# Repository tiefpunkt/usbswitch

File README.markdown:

# USB Switch
The USB Switch will be a device that can be plugged between a PC and a device using USB as a power source. The USB Switch can switch the connected device on and off, controlled by a serial console.

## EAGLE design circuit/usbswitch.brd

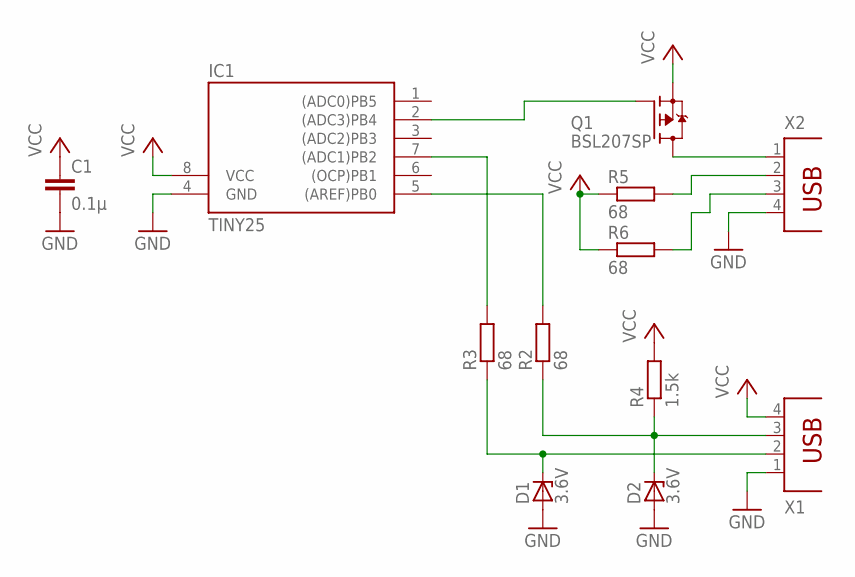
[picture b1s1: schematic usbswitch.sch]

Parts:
C1: 0.1µ; C1206
D1, D2: 3.6V; SOD80C
IC1: TINY25; SOIC8
Q1: BSL207SP; SOT23
R2, R3, R6: 68; R1206
R4: 1.5k; R1206
R5: 68; R1206@1
X1, X2: PN87520

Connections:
GND: C1.2, D1.A, D2.A, IC1.4 (GND), X1.1, X2.4
unnamed: IC1.2 ((ADC3)PB4), Q1.1 (G)
unnamed: Q1.3 (D), X2.1
unnamed: R5.2, X2.2
unnamed: D2.C, R2.1, R4.1, X1.3
unnamed: D1.C, R3.1, X1.2
unnamed: IC1.5 ((AREF)PB0), R2.2
unnamed: IC1.7 ((ADC1)PB2), R3.2
unnamed: R6.2, X2.3
VCC: C1.1, IC1.8 (VCC), Q1.2 (S), R4.2, R5.1, R6.1, X1.4

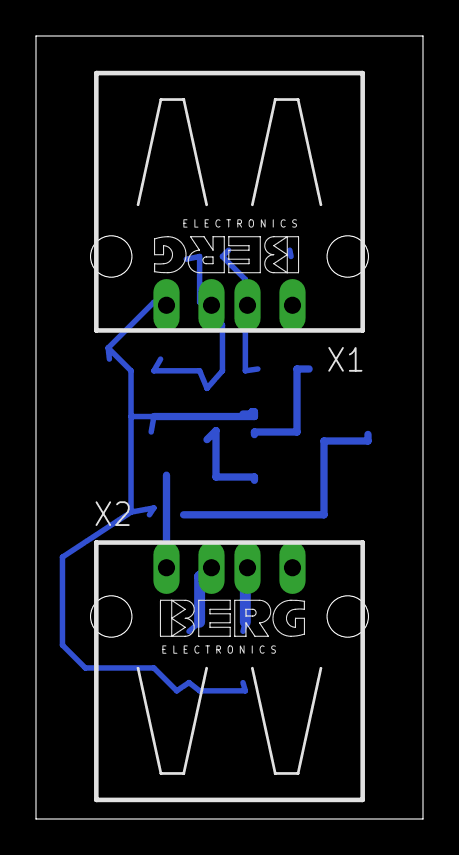
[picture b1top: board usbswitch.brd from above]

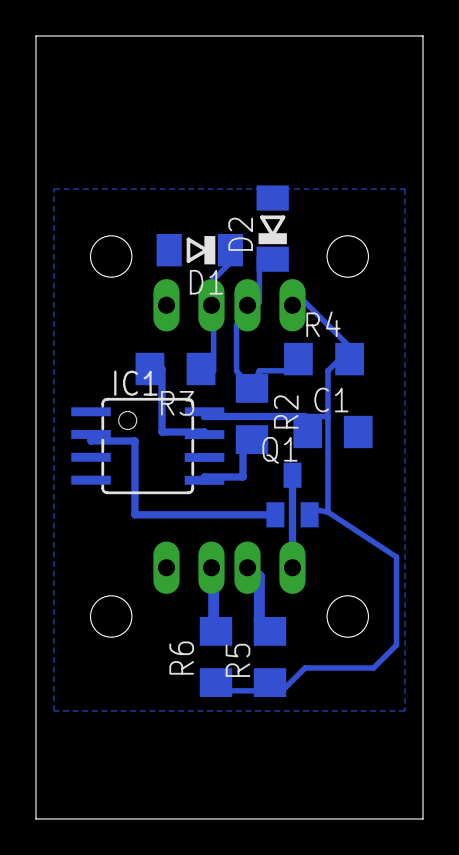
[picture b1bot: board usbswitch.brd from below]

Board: 2 copper layers, 21.5 x 43.5 mm, 12 parts (10 on the bottom side), 10 nets.

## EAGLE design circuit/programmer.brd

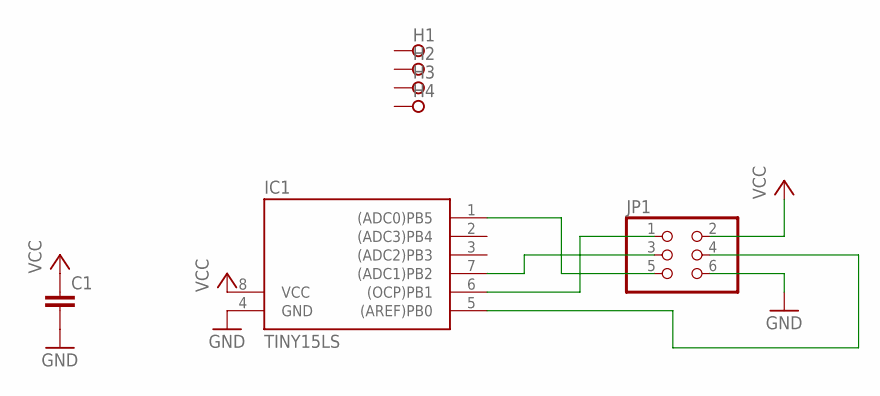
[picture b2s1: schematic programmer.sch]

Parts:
C1: C-EUC1206; C1206
H1, H2, H3, H4: SPECIAL_DRILL_0.1000; PAD_0.1000
IC1: TINY15LS; SOIC8
JP1: PINHD-2X3; 2X03

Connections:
GND: C1.2, IC1.4 (GND), JP1.6
unnamed: IC1.1 ((ADC0)PB5), JP1.5
unnamed: IC1.6 ((OCP)PB1), JP1.1
unnamed: IC1.5 ((AREF)PB0), JP1.4
unnamed: IC1.7 ((ADC1)PB2), JP1.3
VCC: C1.1, IC1.8 (VCC), JP1.2

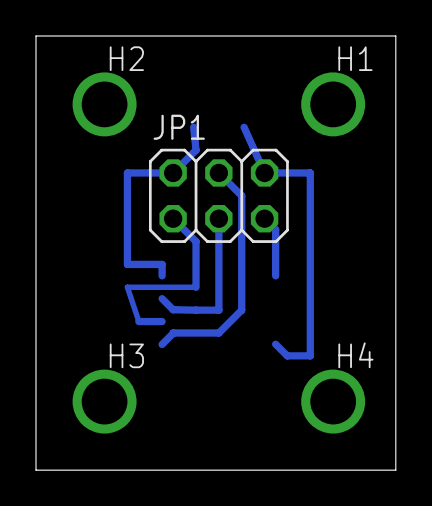
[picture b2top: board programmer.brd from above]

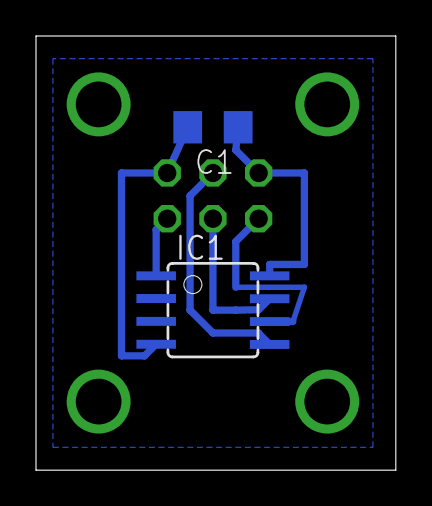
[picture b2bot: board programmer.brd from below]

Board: 2 copper layers, 20.0 x 24.1 mm, 7 parts (2 on the bottom side), 6 nets.

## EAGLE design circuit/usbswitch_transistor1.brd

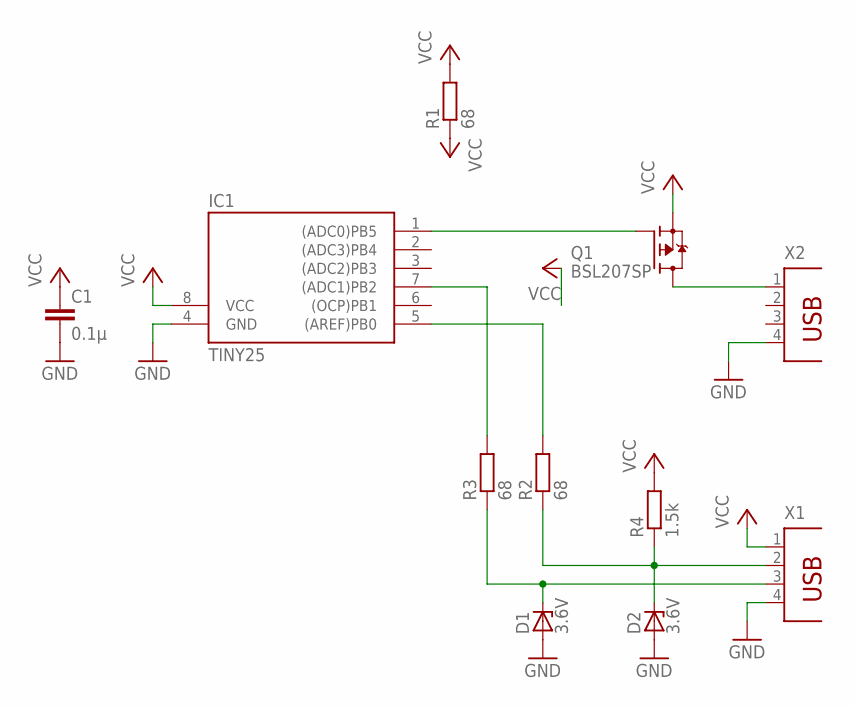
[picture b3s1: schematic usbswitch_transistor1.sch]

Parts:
C1: 0.1µ; C1206
D1, D2: 3.6V; SOD80C
IC1: TINY25; SOIC8
Q1: BSL207SP; SOT23
R1: 68; R1206
R2, R3: 68; R0805
R4: 1.5k; R0805
X1, X2: PN87520

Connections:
GND: C1.2, D1.A, D2.A, IC1.4 (GND), X1.4, X2.4
unnamed: IC1.1 ((ADC0)PB5), Q1.1 (G)
unnamed: Q1.3 (D), X2.1
unnamed: D2.C, R2.1, R4.1, X1.2
unnamed: D1.C, R3.1, X1.3
unnamed: IC1.5 ((AREF)PB0), R2.2
unnamed: IC1.7 ((ADC1)PB2), R3.2
VCC: C1.1, IC1.8 (VCC), Q1.2 (S), R1.1, R1.2, R4.2, X1.1

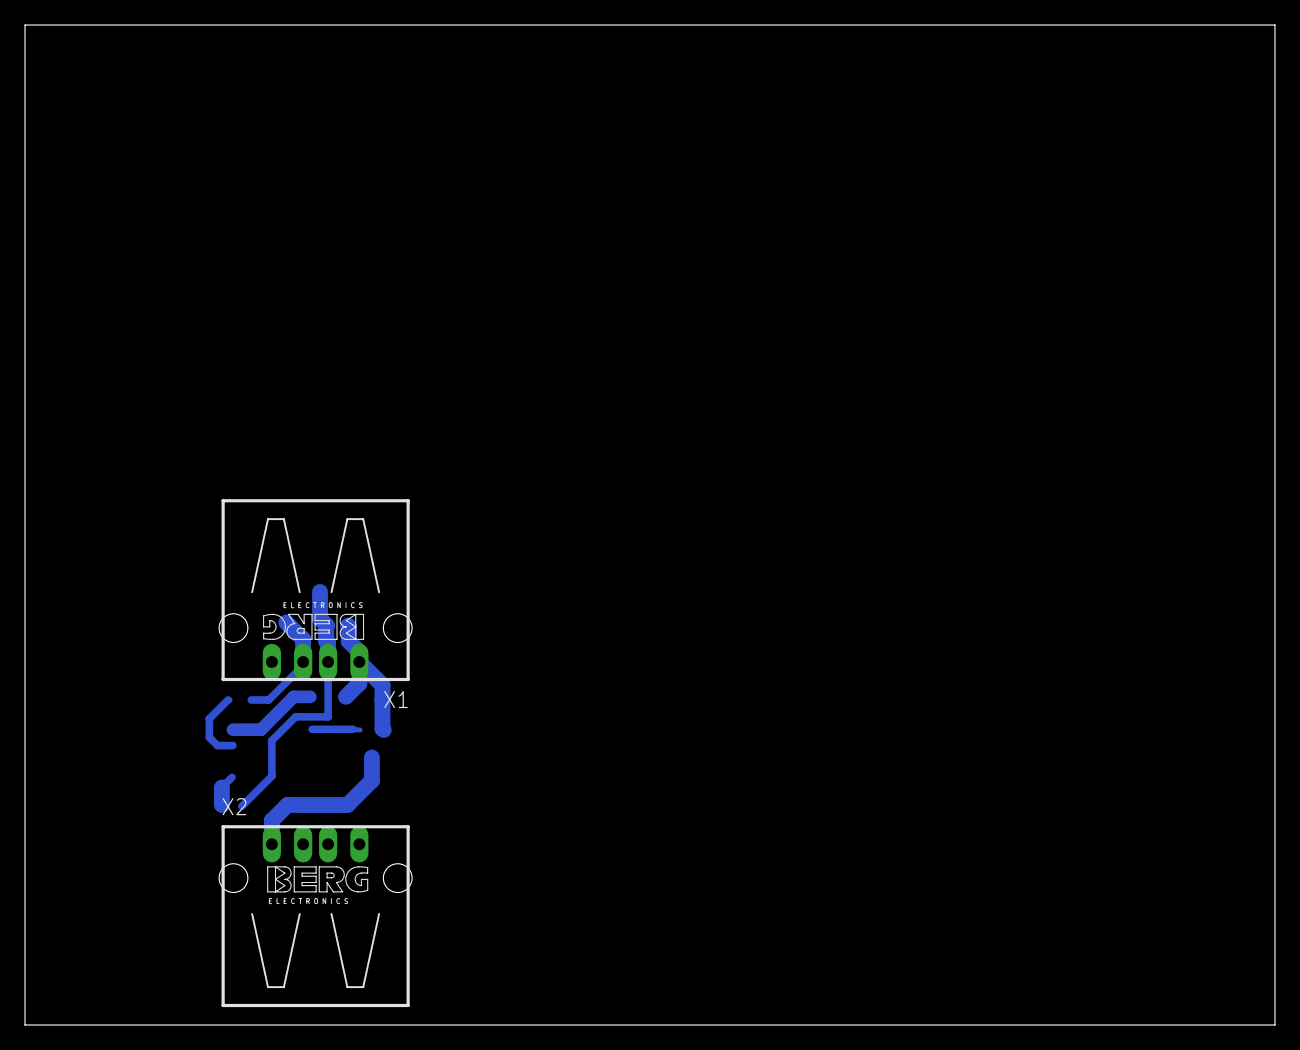
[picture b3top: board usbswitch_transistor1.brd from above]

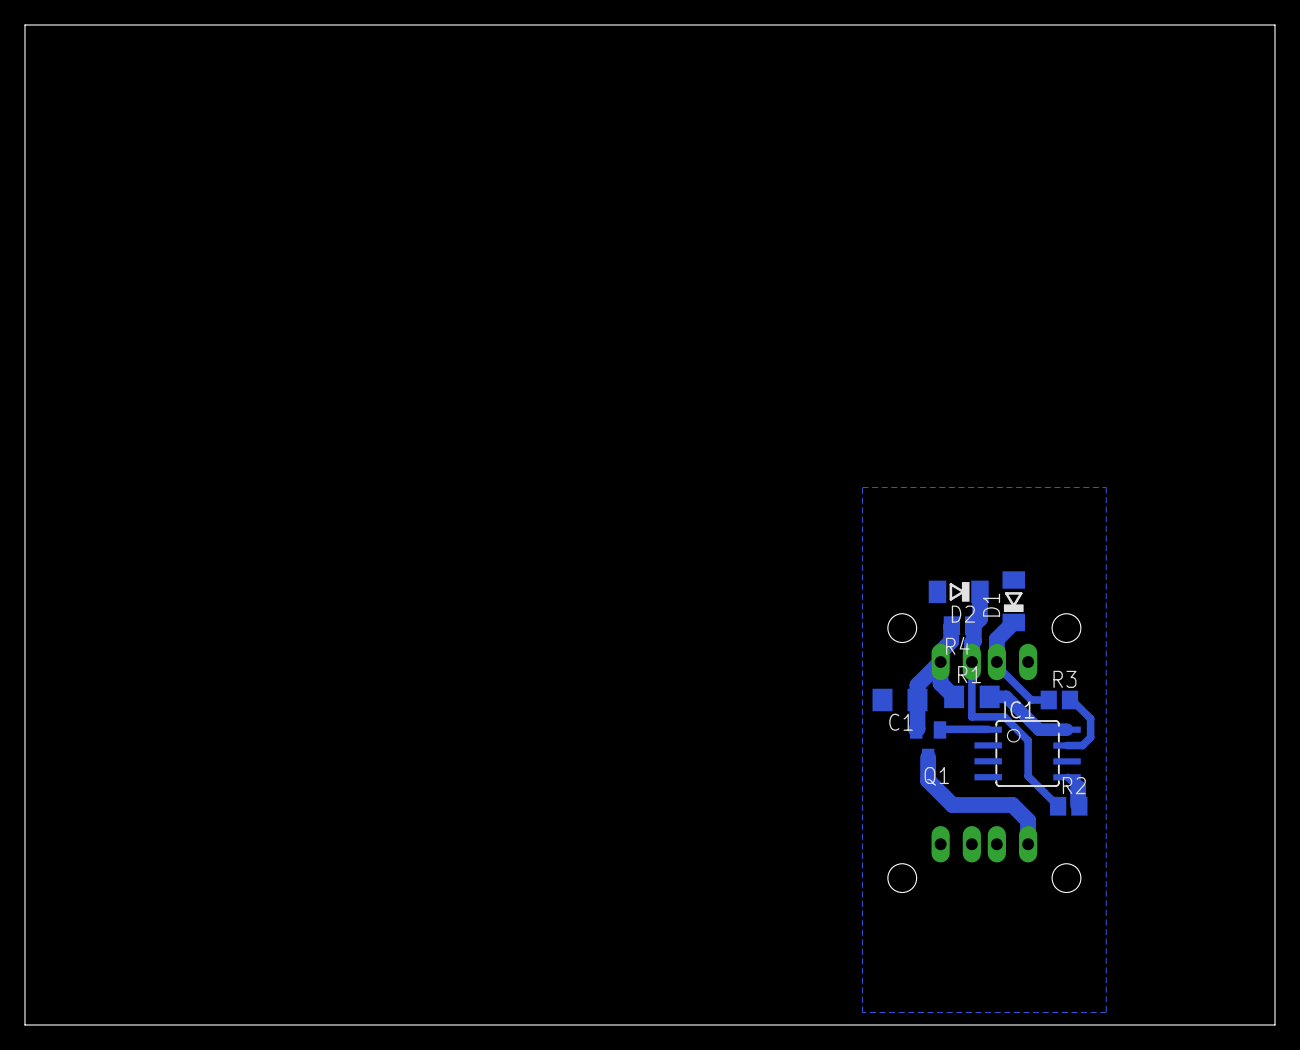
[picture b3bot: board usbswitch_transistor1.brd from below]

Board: 2 copper layers, 100.0 x 80.0 mm, 11 parts (9 on the bottom side), 8 nets.

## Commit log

2012-04-26 .gitignore, Brainstorming and more circuit magic
2012-04-27 SMD-Varianten
2012-06-14 cleanup
2012-06-15 created programmer
2012-06-21 Lessons learned from first smd prototype
    * turned USB connector to PC around
    * made all resistors 1206 types
    * still need to fix transistor stuff...
